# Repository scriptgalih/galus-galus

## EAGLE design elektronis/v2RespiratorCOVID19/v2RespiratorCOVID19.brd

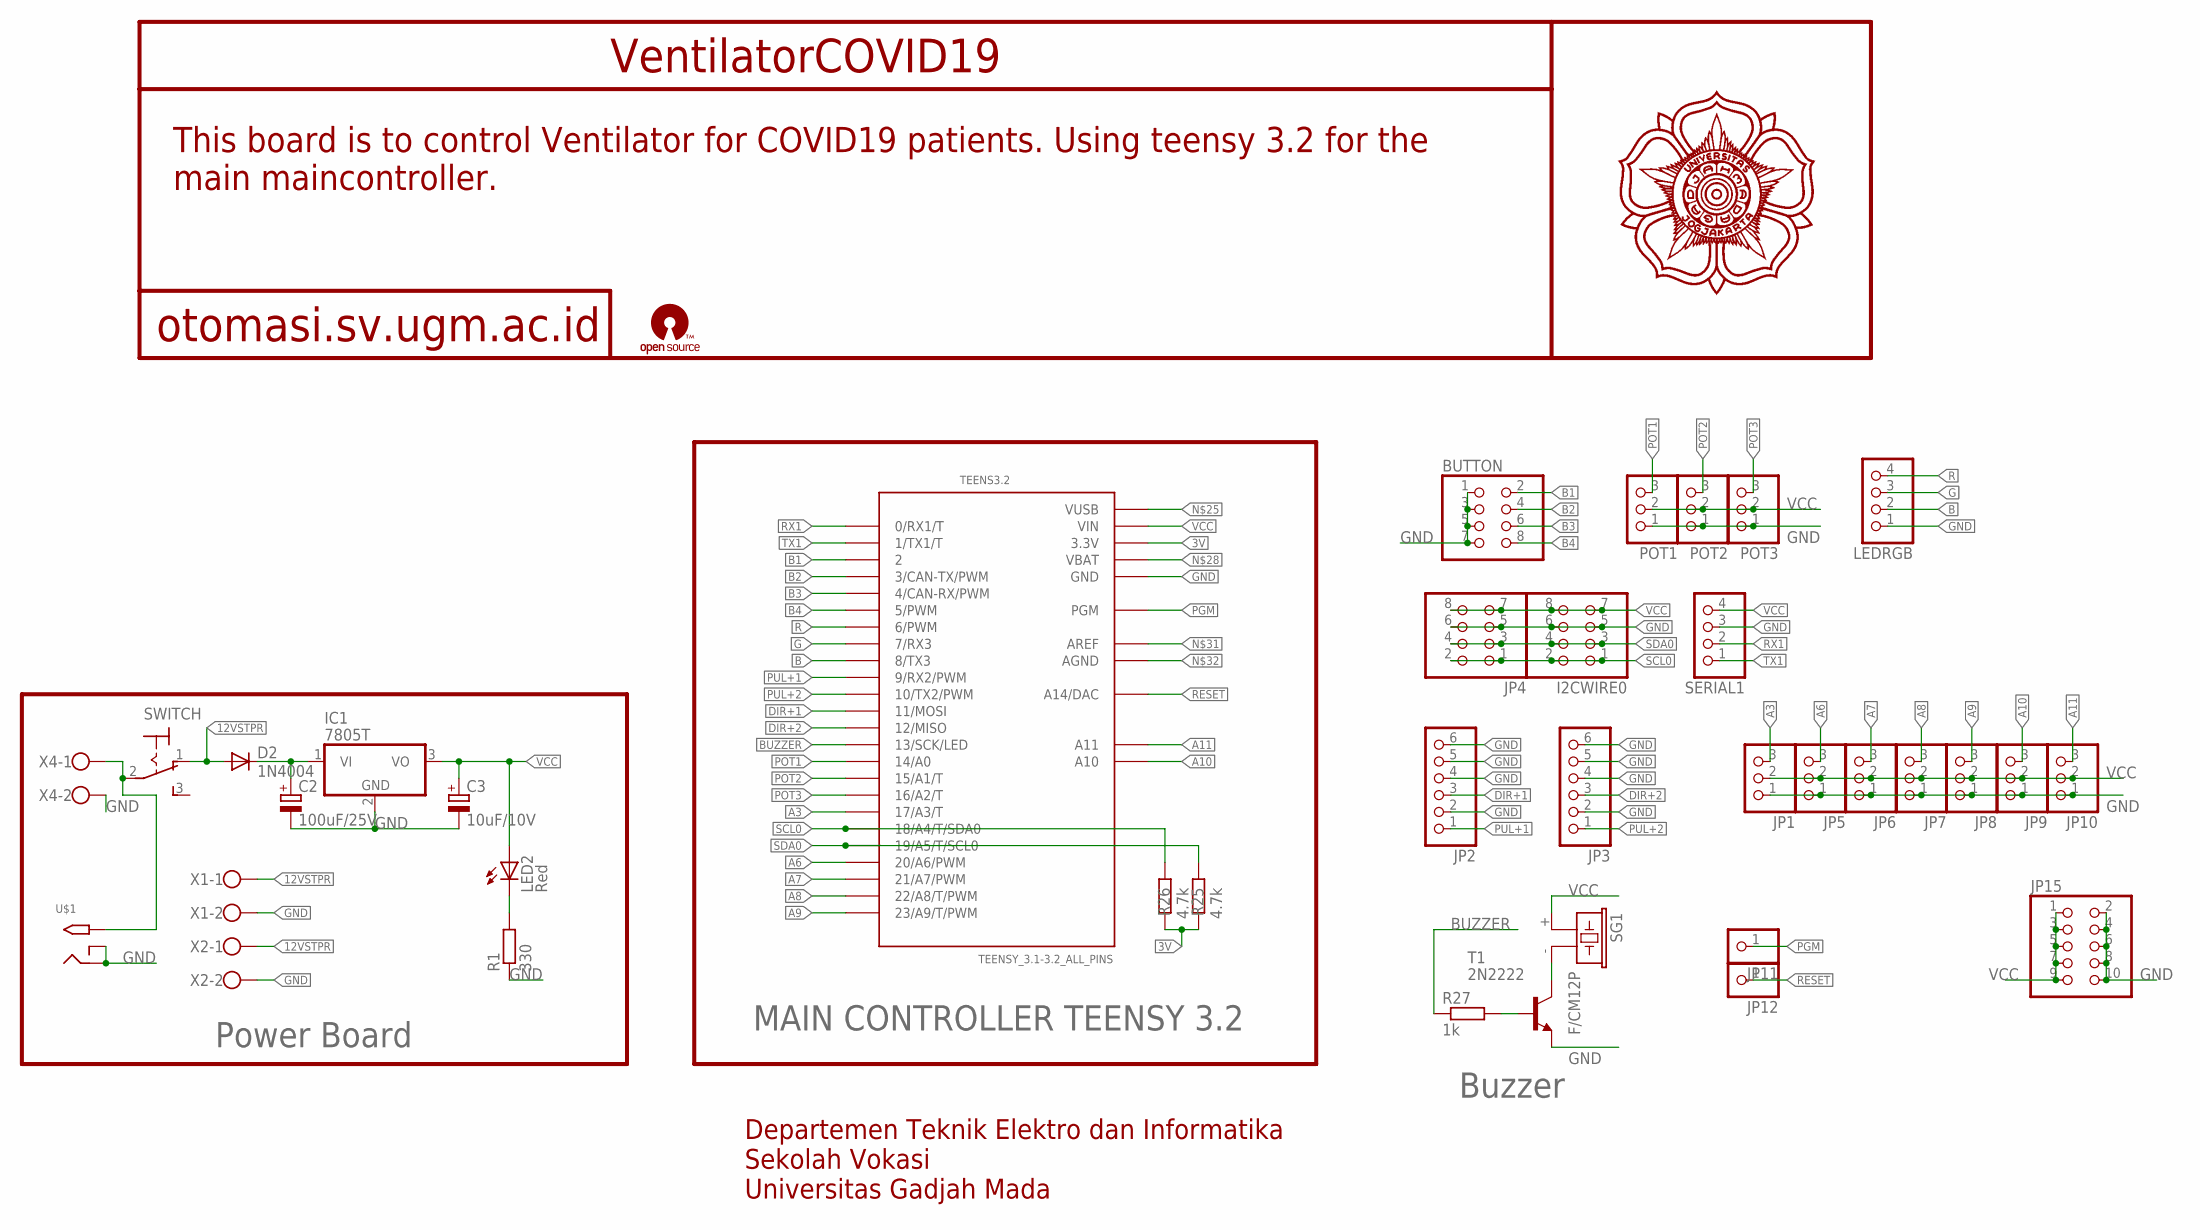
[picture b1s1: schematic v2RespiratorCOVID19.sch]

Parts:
BUTTON: PINHD-2X4; 2X04
C2: 100uF/25V; E5-8,5
C3: 10uF/10V; E5-8,5
D2: 1N4004; DO41-10
I2CWIRE0: PINHD-2X4; 2X04
IC1: 7805T; TO220H
JP1, JP5, JP6, JP7, JP8, JP9, JP10: PINHD-1X3; 1X03
JP2, JP3: PINHD-1X6; 1X06
JP4: PINHD-2X4; 2X04
JP11, JP12: PINHD-1X1; 1X01
JP15: PINHD-2X5; 2X05
LED2: Red; LED3MM
LEDRGB: PINHD-1X4; 1X04
POT1, POT2, POT3: PINHD-1X3; 1X03
R1: 330; R1206
R25, R26: 4.7k; R1206
R27: 1k; R1206
SERIAL1: PINHD-1X4; 1X04
SG1: F/CM12P
SWITCH: M9040P
T1: 2N2222; TO92-EBC-OVAL
TEENS3.2: TEENSY_3.1-3.2_ALL_PINS; TEENSY_3.0-3.2&LC_ALL_PINS
U$1: 2.1MMJACKTHM; PJ-102A
X1, X2, X4: W237-102

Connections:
3V: R25.2, R26.2, TEENS3.2.3.3V, TEENS3.2.3.3V1 (3.3V)
12VSTPR: D2.A, SWITCH.1 (O), X1.1, X2.1
A3: JP1.3, TEENS3.2.17/A3 (17/A3/T)
A6: JP5.3, TEENS3.2.20/A6 (20/A6/PWM)
A7: JP6.3, TEENS3.2.21/A7 (21/A7/PWM)
A8: JP7.3, TEENS3.2.22/A8 (22/A8/T/PWM)
A9: JP8.3, TEENS3.2.23/A9 (23/A9/T/PWM)
A10: JP9.3, TEENS3.2.A10
A11: JP10.3, TEENS3.2.A11
B: LEDRGB.2, TEENS3.2.8 (8/TX3)
B1: BUTTON.2, TEENS3.2.2
B2: BUTTON.4, TEENS3.2.3 (3/CAN-TX/PWM)
B3: BUTTON.6, TEENS3.2.4 (4/CAN-RX/PWM)
B4: BUTTON.8, TEENS3.2.5 (5/PWM)
BUZZER: R27.1, TEENS3.2.13 (13/SCK/LED)
DIR+1: JP2.3, TEENS3.2.11 (11/MOSI)
DIR+2: JP3.3, TEENS3.2.12 (12/MISO)
G: LEDRGB.3, TEENS3.2.7 (7/RX3)
GND: BUTTON.1, BUTTON.3, BUTTON.5, BUTTON.7, C2.-, C3.-, I2CWIRE0.5, I2CWIRE0.6, IC1.2 (GND), JP1.1, JP2.2, JP2.4, JP2.5, JP2.6, JP3.2, JP3.4, JP3.5, JP3.6, JP4.5, JP4.6, JP5.1, JP6.1, JP7.1, JP8.1, JP9.1, JP10.1, JP15.2, JP15.4, JP15.6, JP15.8, JP15.10, LEDRGB.1, POT1.1, POT2.1, POT3.1, R1.1, SERIAL1.3, T1.E, TEENS3.2.GND, TEENS3.2.GND1 (GND), U$1.RING, U$1.RING_SW, X1.2, X2.2, X4.2
unnamed: R27.2, T1.B
unnamed: C2.+, D2.C, IC1.1 (VI)
unnamed: SG1.- (2), T1.C
unnamed: LED2.K (C), R1.2
unnamed: SWITCH.2, U$1.TIP, X4.1
PGM: JP11.1, TEENS3.2.PGM
POT1: POT1.3, TEENS3.2.14/A0
POT2: POT2.3, TEENS3.2.15/A1 (15/A1/T)
POT3: POT3.3, TEENS3.2.16/A2 (16/A2/T)
PUL+1: JP2.1, TEENS3.2.9 (9/RX2/PWM)
PUL+2: JP3.1, TEENS3.2.10 (10/TX2/PWM)
R: LEDRGB.4, TEENS3.2.6 (6/PWM)
RESET: JP12.1, TEENS3.2.RESET/DAC (A14/DAC)
RX1: SERIAL1.2, TEENS3.2.0 (0/RX1/T)
SCL0: I2CWIRE0.1, I2CWIRE0.2, JP4.1, JP4.2, R26.1, TEENS3.2.18/A4 (18/A4/T/SDA0)
SDA0: I2CWIRE0.3, I2CWIRE0.4, JP4.3, JP4.4, R25.1, TEENS3.2.19/A5 (19/A5/T/SCL0)
TX1: SERIAL1.1, TEENS3.2.1 (1/TX1/T)
VCC: C3.+, I2CWIRE0.7, I2CWIRE0.8, IC1.3 (VO), JP1.2, JP4.7, JP4.8, JP5.2, JP6.2, JP7.2, JP8.2, JP9.2, JP10.2, JP15.1, JP15.3, JP15.5, JP15.7, JP15.9, LED2.A, POT1.2, POT2.2, POT3.2, SERIAL1.4, SG1.+ (1), TEENS3.2.VIN

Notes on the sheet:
MAIN CONTROLLER TEENSY 3.2
Departemen Teknik Elektro dan Informatika Sekolah Vokasi Universitas Gadjah Mada
Buzzer
Power Board
VentilatorCOVID19
otomasi.sv.ugm.ac.id
This board is to control Ventilator for COVID19 patients. Using teensy 3.2 for the main maincontroller.

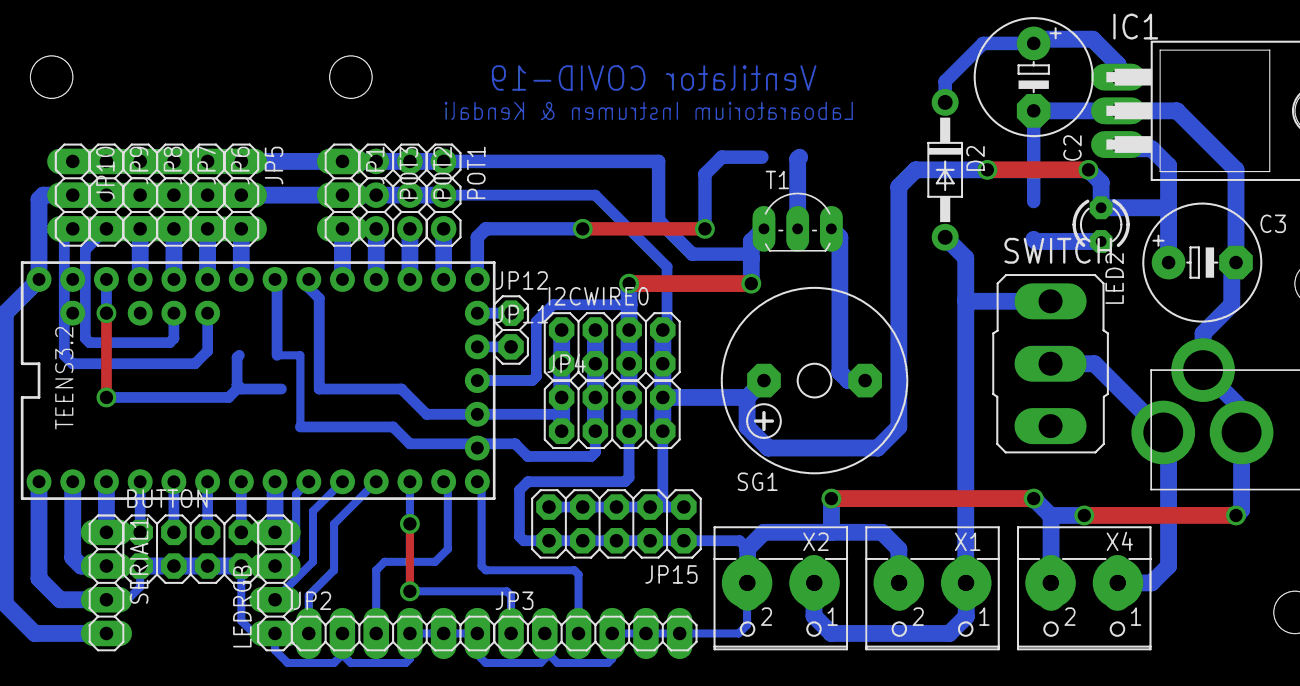
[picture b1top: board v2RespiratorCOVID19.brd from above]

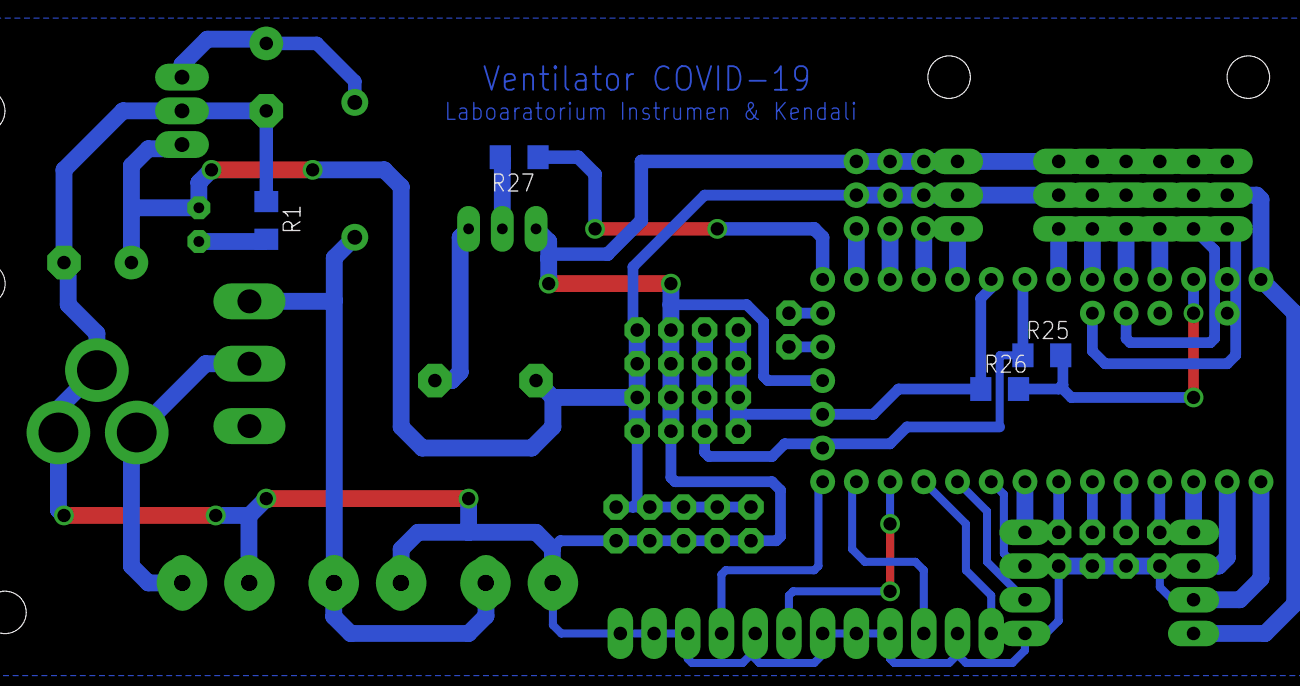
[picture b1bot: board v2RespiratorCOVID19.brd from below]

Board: 2 copper layers, 37 parts (4 on the bottom side), 37 nets.

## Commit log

2020-04-24 base program dari tirza
2020-04-24 elektronis dari tirza
